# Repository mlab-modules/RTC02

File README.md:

[Czech](./README.cs.md)
<!--- module --->
# RTC02A - High-accuracy I2C Real Time Clock module

Real-Time Clock controlled through I2C with battery backup. The accuracy is in the order of 20 ppm.

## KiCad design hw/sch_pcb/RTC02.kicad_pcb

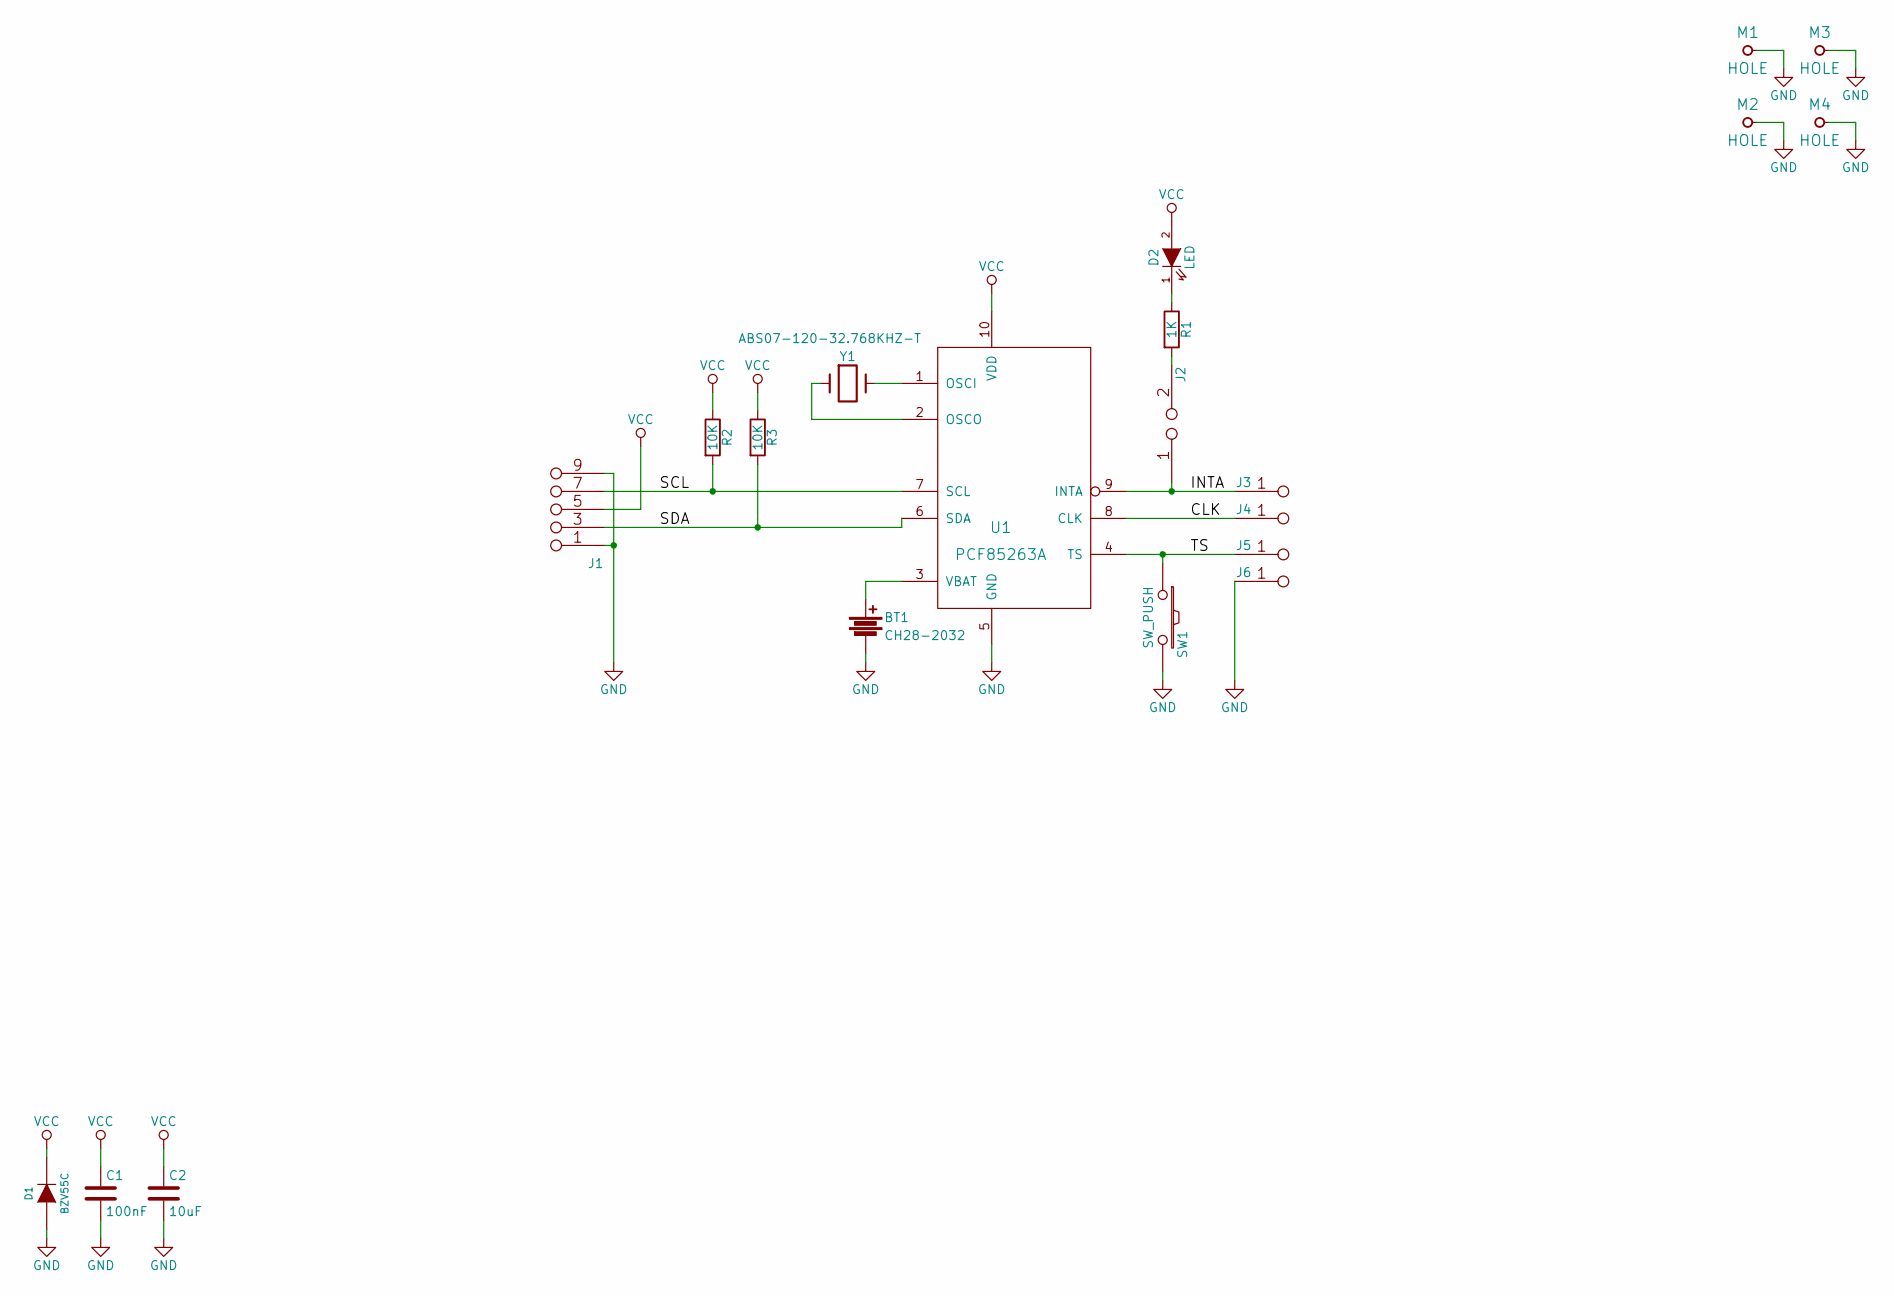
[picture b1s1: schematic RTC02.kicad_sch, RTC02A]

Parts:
BT1: CH28-2032
C1: 100nF; SMD-0805
C2: 10uF; SMD-0805
D1: BZV55C; Diode-MiniMELF_Standard
D2: LED; LED_1206
J1: JUMP_5X2; Straight_2x05
J2: JUMP2_2x1; Straight_2x01
J3, J4, J5, J6: JUMP_2x1; Straight_2x01
M1, M2, M3, M4: HOLE; MountingHole_3mm
R1: 1K; SMD-0805
R2, R3: 10K; SMD-0805
SW1: SW_PUSH; SW_PUSH_SMALL
U1: PCF85263A; TSSOP-10_3x3mm_Pitch0.5mm
Y1: ABS07-120-32.768KHZ-T; ABS07

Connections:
/CLK: J4.1, J4.2, U1.8 (CLK)
/INTA: J2.1, J3.1, J3.2, U1.9 (INTA)
/SCL: J1.7, J1.8 (7), R2.2, U1.7 (SCL)
/SDA: J1.3 (4), J1.4, R3.2, U1.6 (SDA)
/TS: J5.1, J5.2, SW1.1, U1.4 (TS)
GND: BT1.2, C1.2, C2.2, D1.2 (A), J1.1 (2), J1.2, J1.9 (10), J1.10, J6.1, J6.2, M1.1, M2.1, M3.1, M4.1, SW1.2, U1.5 (GND)
unnamed: BT1.1, U1.3 (VBAT)
unnamed: D2.1 (K), R1.1
unnamed: J2.2, R1.2
unnamed: U1.1 (OSCI), Y1.2
unnamed: U1.2 (OSCO), Y1.1
VCC: C1.1, C2.1, D1.1 (K), D2.2 (A), J1.5 (6), J1.6, R2.1, R3.1, U1.10 (VDD)

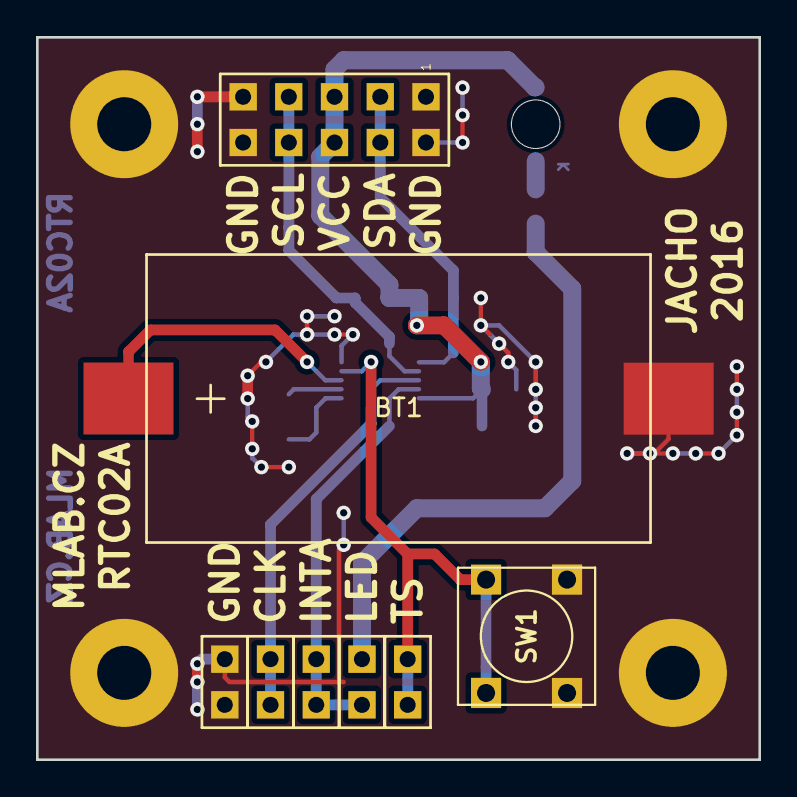
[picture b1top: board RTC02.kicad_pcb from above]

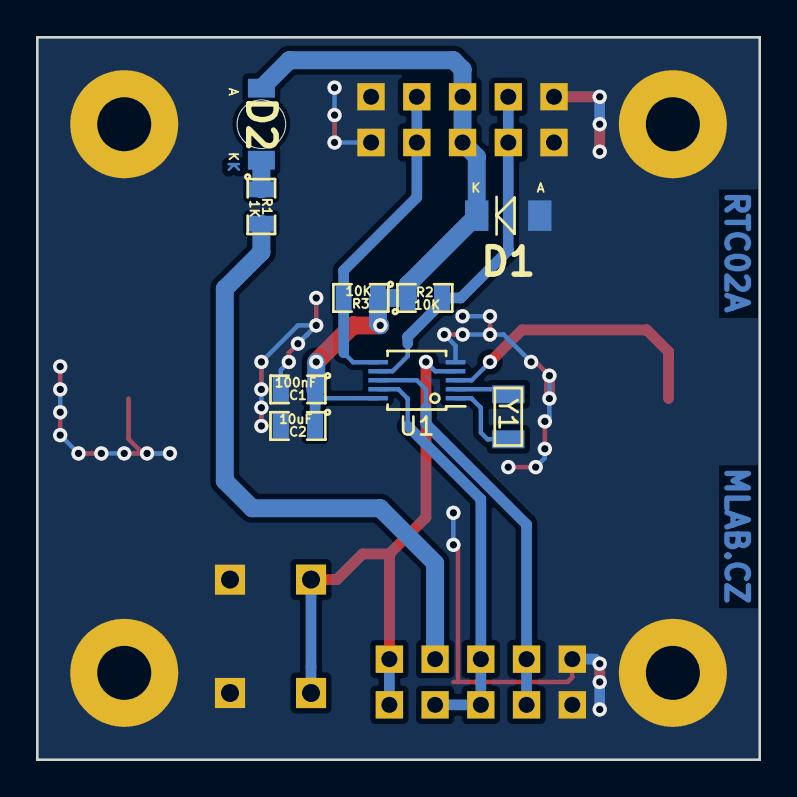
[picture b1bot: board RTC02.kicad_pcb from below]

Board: 2 copper layers, 40.1 x 40.1 mm, 21 parts (9 on the bottom side), 12 nets.

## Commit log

2023-04-01 Adding force option to enable splitting in not fresh copy of Modules repository.
2023-07-05 automated commit; add github actions
2023-07-05 Update metadata files
2023-07-05 automated commit; rename source files to new naming convence
2023-07-05 Update workflow files
2023-09-16 Update status
2023-09-17 Update project to KiCAD7.
2023-09-17 Update actions products
2023-09-17 Update metadata.yaml
    set title image.
